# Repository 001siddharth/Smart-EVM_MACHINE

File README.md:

# Smart-EVM_MACHINE
**Approach Used** 
- We have stored the votes of each candidate in SR Latches and after the completion of 15 
sec from the first press of voters, the votes will be stored in the counter accumulating all the 
votes from different voters. At the end, you may press a push button to display the winner on 
7-Segment Display <br>
        **Features Added** <br>
  - Votes Comparator: The button named “Display Winner” when pressed compares the votes of all  
four candidates and prints ‘0’ if A wins, ‘1’ if B wins, ‘2’ if C wins, and ‘3’ if D wins. The 
comparator uses 3 four-bit comparator and 2 multiplexers
  - Display of Winner: The winner as output from comparator is shown on a 7-Segment Display for better 
readability on PCB. The Display will only function when the Display Winner button is 
pressed
  - MULTIPLE CANDIDATE VOTING: A voter may cast his vote(s) to any of the four candidates (one or more than one 
candidate) while only once for one candidate. The voter has a total time of 15 seconds in 
which he may cast his votes after which his votes will be registered
  - “Voted For” LEDs: Added four LEDs that display for which candidate the voter has voted. This feature 
removes any uncertainty in the minds of the voter that they might cast a wrong vote. A visual 
confirmation is the best way to remove any such confusion

  - REVERSE THE CASTED VOTE: As the votes are not registered into counters until 15 seconds have passed. The voter has this 15 seconds to alter his voting decisions. We have added four additional buttons to reverse a vote that voter may have casted mistakenly
    
  -  The ‘READY’ LED: As the votes are not registered into counters until 15 seconds have passed. The voter has this 15 seconds to alter his voting 
decisions. We have added four additional buttons to reverse a vote that voter may have cast mistakenly
  - 3 SECOND DELAY : 3-second delay is added after any button to cast a vote is pressed by the voter. 
This feature is to avoid any debouncing caused by the switch. However, as we are using SR 
Latch, which once set will not change its value until reset, overcomes this issue of 
debouncing without introducing any delay in the circuit.<br><br>
                                **PCB-layout**
<br><br>
Here as you can see in this PCB layout design we have generated the clock pulse of 
frequency 1Hz using N555 and with some resistors and capacitors. Each logic gate and 
IC’s VCC and GND terminal is connected with a connector with two inputs. Through pin
no.1 of the connector, we will supply VCC of 5V and Ground through pin no 2. Also, there 
is enable pin which will be activated by supplying 5V. And after enabling it will start 
comparing the votes of the candidates. And the result will be shown In the display attached.
We have done copper filling of Ground only because Filling a via with copper increases its 
thermal conductivity and higher conductivity will lead to high heat and may overheat the 
whole board and also may damage IC’s

<br> 
The Schematic of the Circuit <br>

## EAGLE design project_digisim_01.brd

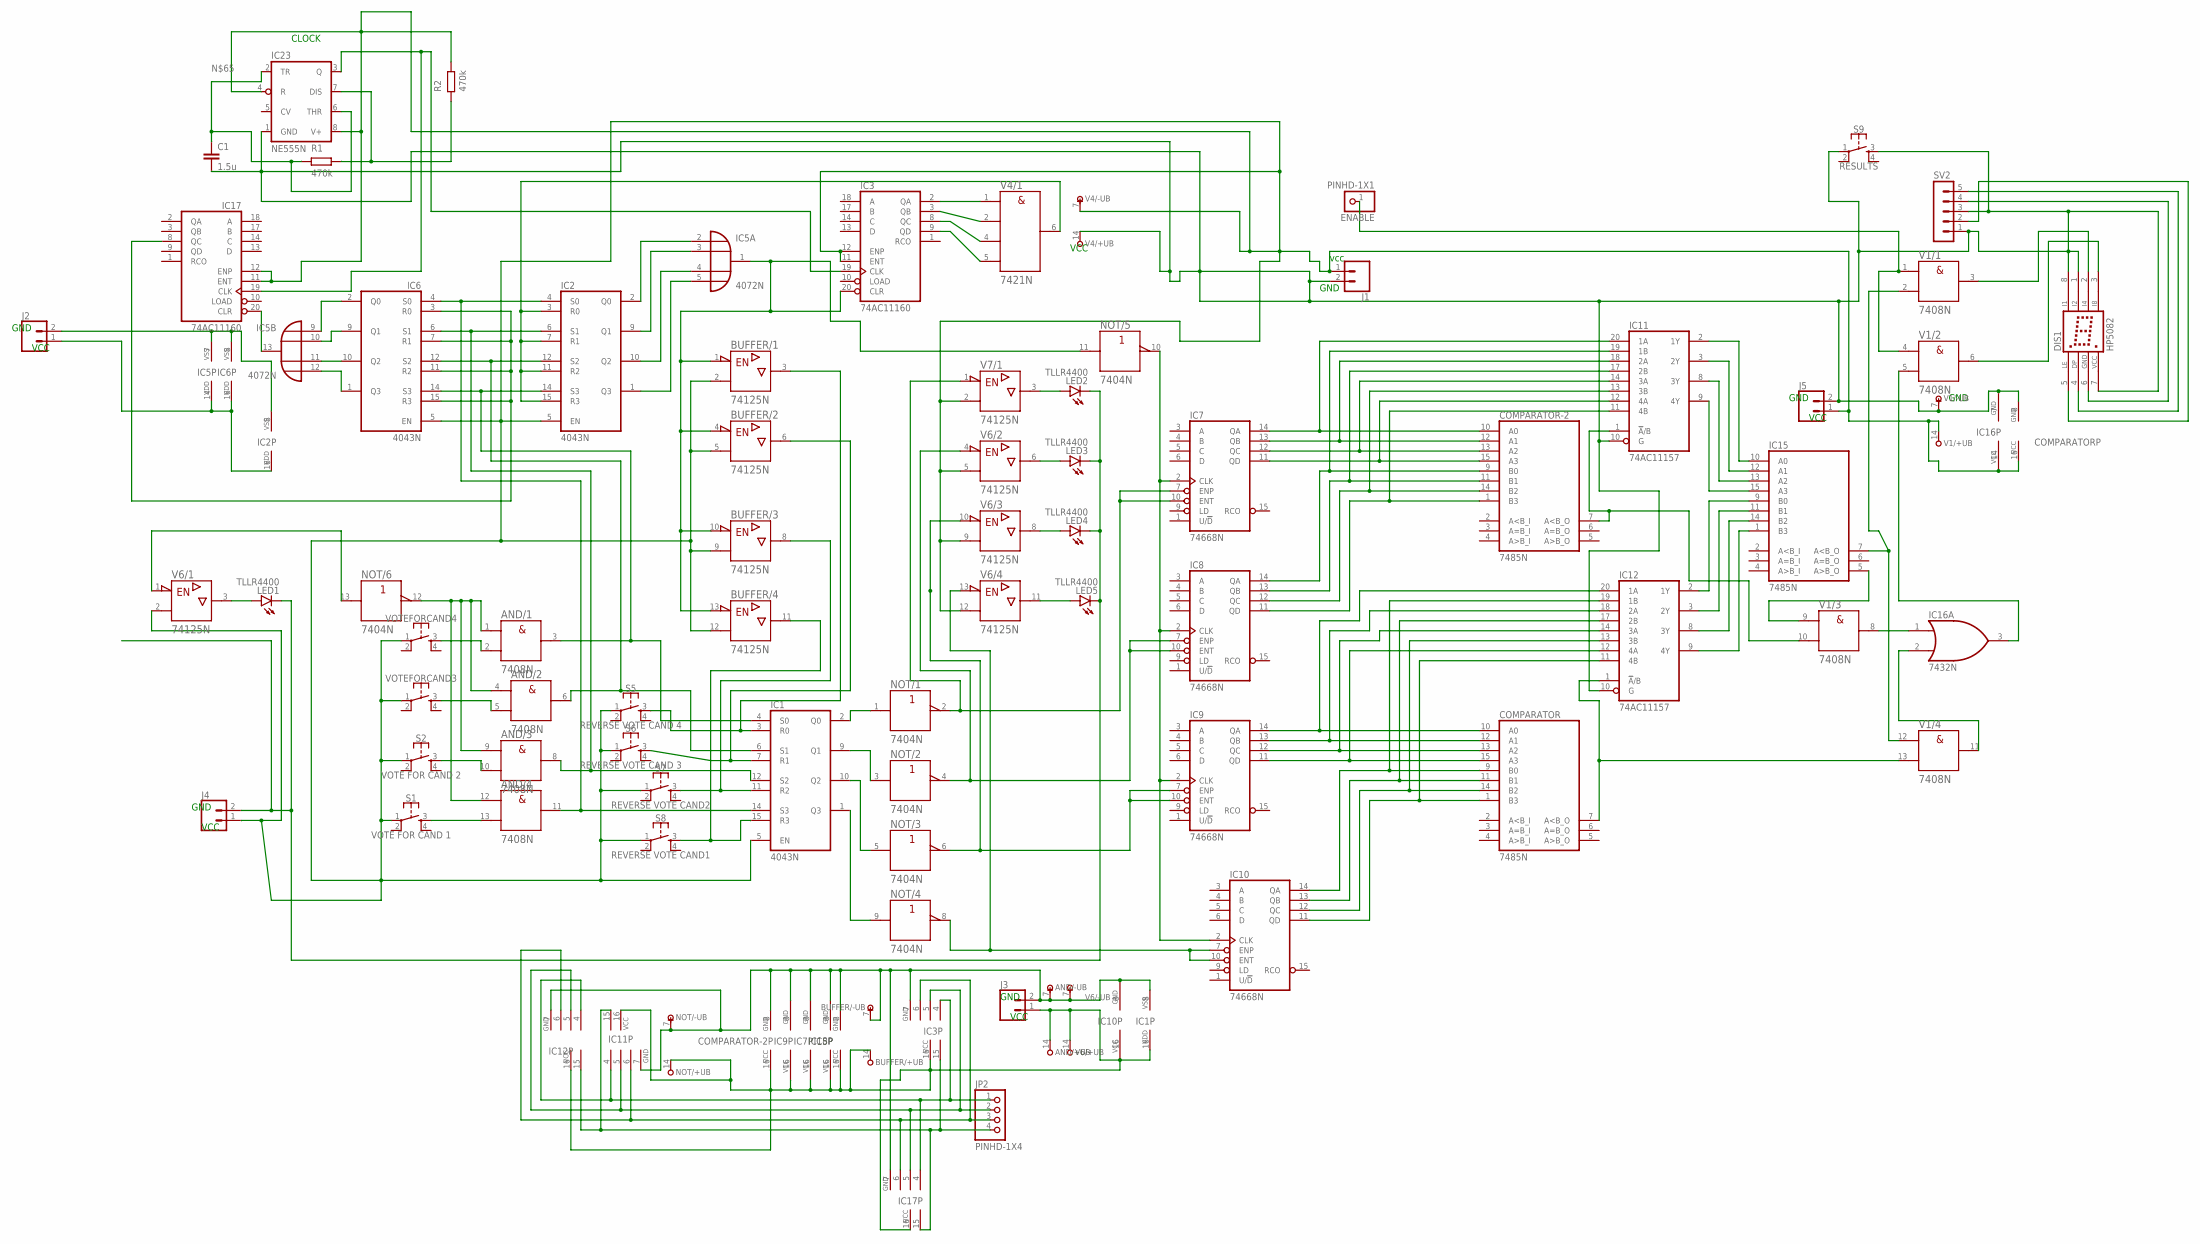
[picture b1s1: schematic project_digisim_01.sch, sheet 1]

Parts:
AND: 7408N; DIL14
BUFFER: 74125N; DIL14
C1: 1.5u; C2.5-3
COMPARATOR: 7485N; DIL16
COMPARATOR-2: 7485N; DIL16
DIS1: HP5082
ENABLE: PINHD-1X1; 1X01
IC1, IC2, IC6: 4043N; DIL16
IC3, IC17: 74AC11160; DIL20
IC5: 4072N; DIL14
IC7, IC8, IC9, IC10: 74668N; DIL16
IC11, IC12: 74AC11157; DIL20
IC15: 7485N; DIL16
IC16: 7432N; DIL14
IC23: NE555N; DIL08
J1, J2, J3, J4, J5: CONN_02LOCK; 1X02_LOCK
JP2: PINHD-1X4; 1X04
LED1, LED2, LED3, LED4, LED5: TLLR4400; LED3MM
NOT: 7404N; DIL14
S1: VOTE FOR CAND 1; TACTILE_SWITCH_SMD_4.6X2.8MM
S2: VOTE FOR CAND 2; TACTILE_SWITCH_SMD_4.6X2.8MM
S5: REVERSE VOTE CAND 4; TACTILE_SWITCH_SMD_4.6X2.8MM
S6: REVERSE VOTE CAND 3; TACTILE_SWITCH_SMD_4.6X2.8MM
S7: REVERSE VOTE CAND2; TACTILE_SWITCH_SMD_4.6X2.8MM
S8: REVERSE VOTE CAND1; TACTILE_SWITCH_SMD_4.6X2.8MM
S9: RESULTS; TACTILE_SWITCH_SMD_4.6X2.8MM
SV2: MA05-1
V1: 7408N; DIL14
V4: 7421N; DIL14
V6, V7: 74125N; DIL14
VOTEFORCAND3, VOTEFORCAND4: MOMENTARY-SWITCH-SPST-2-SMD-4.6X2.8MM; TACTILE_SWITCH_SMD_4.6X2.8MM

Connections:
+UB: V7.14 (+UB)
-UB: V7.7 (-UB)
unnamed: AND.3 (Y), IC1.4 (S0), IC2.14 (S3), IC6.14 (S3)
unnamed: IC10.7 (ENP), IC10.10 (ENT), NOT.8 (Y), V6.13 (!G)
unnamed: IC2.2 (Q0), IC5.2 (I0)
unnamed: AND.8 (Y), IC1.12 (S2), IC2.6 (S1), IC6.6 (S1)
unnamed: DIS1.3 (I8), V1.6 (Y)
unnamed: BUFFER.3 (Y), IC1.3 (R0), S5.3
unnamed: BUFFER.6 (Y), IC1.7 (R1), S6.3
unnamed: BUFFER.11 (Y), IC1.15 (R3), S8.3
unnamed: IC1.2 (Q0), NOT.1 (A)
unnamed: IC1.9 (Q1), NOT.3 (A)
unnamed: NOT.13 (A), V6.1 (!G)
unnamed: IC1.10 (Q2), NOT.5 (A)
unnamed: LED2.A, V7.3 (Y)
unnamed: IC1.1 (Q3), NOT.9 (A)
unnamed: LED3.A, V6.6 (Y)
unnamed: IC7.7 (ENP), IC7.10 (ENT), NOT.2 (Y), V7.1 (!G)
unnamed: IC16.1 (I0), V1.8 (Y)
unnamed: IC2.8 (VSS), IC5.7 (VSS), IC6.8 (VSS), J2.2
unnamed: COMPARATOR-2.10 (A0), IC7.14 (QA), IC11.20 (1A)
unnamed: COMPARATOR-2.12 (A1), IC7.13 (QB), IC11.18 (2A)
unnamed: LED4.A, V6.8 (Y)
unnamed: COMPARATOR-2.13 (A2), IC7.12 (QC), IC11.14 (3A)
unnamed: COMPARATOR-2.15 (A3), IC7.11 (QD), IC11.12 (4A)
unnamed: COMPARATOR-2.9 (B0), IC8.14 (QA), IC11.19 (1B)
unnamed: COMPARATOR-2.11 (B1), IC8.13 (QB), IC11.17 (2B)
unnamed: COMPARATOR-2.14 (B2), IC8.12 (QC), IC11.13 (3B)
unnamed: COMPARATOR-2.1 (B3), IC8.11 (QD), IC11.11 (4B)
unnamed: COMPARATOR.10 (A0), IC9.14 (QA), IC12.20 (1A)
unnamed: COMPARATOR.12 (A1), IC9.13 (QB), IC12.18 (2A)
unnamed: COMPARATOR.13 (A2), IC9.12 (QC), IC12.14 (3A)
unnamed: COMPARATOR.15 (A3), IC9.11 (QD), IC12.12 (4A)
unnamed: COMPARATOR.9 (B0), IC10.14 (QA), IC12.19 (1B)
unnamed: COMPARATOR.11 (B1), IC10.13 (QB), IC12.17 (2B)
unnamed: COMPARATOR.14 (B2), IC10.12 (QC), IC12.13 (3B)
unnamed: COMPARATOR.1 (B3), IC10.11 (QD), IC12.11 (4B)
unnamed: IC11.2 (1Y), IC15.10 (A0)
unnamed: IC11.3 (2Y), IC15.12 (A1)
unnamed: IC11.8 (3Y), IC15.13 (A2)
unnamed: IC11.9 (4Y), IC15.15 (A3)
unnamed: IC12.2 (1Y), IC15.9 (B0)
unnamed: IC12.3 (2Y), IC15.11 (B1)
unnamed: IC12.8 (3Y), IC15.14 (B2)
unnamed: IC12.9 (4Y), IC15.1 (B3)
unnamed: COMPARATOR-2.7 (A<B_O), IC11.1 (!A!/B), V1.10 (B)
unnamed: COMPARATOR.7 (A<B_O), IC12.1 (!A!/B), V1.13 (B)
unnamed: AND.11 (Y), IC1.14 (S3), IC2.4 (S0), IC6.4 (S0)
unnamed: IC15.5 (A>B_O), V1.9 (A)
unnamed: ENABLE.1, V1.1 (A), V1.4 (A)
unnamed: IC2.16 (VDD), IC5.14 (VDD), IC6.16 (VDD), J2.1
unnamed: IC16.2 (I1), V1.11 (Y)
unnamed: IC3.19 (CLK), IC17.19 (CLK), IC23.3 (Q)
unnamed: IC2.9 (Q1), IC5.3 (I1)
unnamed: IC2.10 (Q2), IC5.4 (I2)
unnamed: IC2.1 (Q3), IC5.5 (I3)
unnamed: BUFFER.8 (Y), IC1.11 (R2), S7.3
unnamed: LED5.A, V6.11 (Y)
unnamed: IC16.3 (O), V1.5 (B)
unnamed: IC8.7 (ENP), IC8.10 (ENT), NOT.4 (Y), V6.4 (!G)
unnamed: DIS1.2 (I4), V1.3 (Y)
unnamed: IC7.2 (CLK), IC8.2 (CLK), IC9.2 (CLK), IC10.2 (CLK), NOT.10 (Y)
unnamed: J4.2, LED1.K (C), LED2.K (C), LED3.K (C), LED4.K (C), LED5.K (C)
unnamed: IC15.7 (A<B_O), V1.2 (B), V1.12 (A)
unnamed: AND.6 (Y), IC1.6 (S1), IC2.12 (S2), IC6.12 (S2)
unnamed: LED1.A, V6.3 (Y)
unnamed: C1.1, IC23.2 (TR), IC23.6 (THR)
unnamed: AND.2 (B), VOTEFORCAND4.3
unnamed: AND.5 (B), VOTEFORCAND3.3
unnamed: AND.10 (B), S2.3
unnamed: AND.13 (B), S1.3
unnamed: AND.1 (A), AND.4 (A), AND.9 (A), AND.12 (A), NOT.12 (Y)
unnamed: IC3.2 (QA), V4.1 (A)
unnamed: IC3.3 (QB), V4.2 (B)
unnamed: IC3.8 (QC), V4.4 (C)
unnamed: IC3.9 (QD), V4.5 (D)
unnamed: IC2.3 (R0), IC2.7 (R1), IC2.11 (R2), IC2.15 (R3), V4.6 (Y)
unnamed: IC5.13 (O), IC17.20 (CLR)
unnamed: IC5.9 (I0), IC6.2 (Q0)
unnamed: IC5.10 (I1), IC6.9 (Q1)
unnamed: IC5.11 (I2), IC6.10 (Q2)
unnamed: IC5.12 (I3), IC6.1 (Q3)
unnamed: IC6.3 (R0), IC6.7 (R1), IC6.11 (R2), IC6.15 (R3), IC17.8 (QC)
unnamed: BUFFER.2 (A), BUFFER.5 (A), BUFFER.9 (A), BUFFER.12 (A), COMPARATOR.16 (VCC), IC1.5 (EN), IC2.5 (EN), IC3.11 (ENT), IC3.12 (ENP), IC6.5 (EN), IC16.14 (VCC), IC17.11 (ENT), IC17.12 (ENP), IC23.4 (R), IC23.8 (V+), J1.1, J4.1, J5.1, S1.1, S2.1, S5.1, S6.1, S7.1, S8.1, V1.14 (+UB), V4.7 (-UB), V6.2 (A), V6.5 (A), V6.9 (A), V6.12 (A), V7.2 (A), VOTEFORCAND3.1, VOTEFORCAND4.1
unnamed: IC9.7 (ENP), IC9.10 (ENT), NOT.6 (Y), V6.10 (!G)
unnamed: C1.2, COMPARATOR.8 (GND), DIS1.1 (I2), DIS1.7 (VCC), DIS1.8 (I1), IC11.10 (G), IC12.10 (G), IC16.7 (GND), IC23.1 (GND), J1.2, J5.2, S9.1, S9.3, SV2.1, SV2.3, V1.7 (-UB), V4.14 (+UB)
unnamed: DIS1.6 (GND), SV2.4
unnamed: DIS1.4 (DP), SV2.5
unnamed: BUFFER.1 (!G), BUFFER.4 (!G), BUFFER.10 (!G), BUFFER.13 (!G), IC3.20 (CLR), IC5.1 (O), NOT.11 (A)
unnamed: DIS1.5 (LE), SV2.2
unnamed: AND.7 (-UB), BUFFER.7 (-UB), COMPARATOR-2.8 (GND), IC1.8 (VSS), IC3.7 (GND), IC7.8 (GND), IC8.8 (GND), IC9.8 (GND), IC10.8 (GND), IC11.7 (GND), IC12.7 (GND), IC15.8 (GND), IC17.7 (GND), J3.2, NOT.7 (-UB), V6.7 (-UB)
unnamed: AND.14 (+UB), BUFFER.14 (+UB), COMPARATOR-2.16 (VCC), IC1.16 (VDD), IC3.16 (VCC), IC7.16 (VCC), IC8.16 (VCC), IC9.16 (VCC), IC10.16 (VCC), IC11.16 (VCC), IC12.16 (VCC), IC15.16 (VCC), IC17.16 (VCC), J3.1, NOT.14 (+UB), V6.14 (+UB)
unnamed: IC3.4 (GND), IC11.4 (GND), IC12.4 (GND), IC17.4 (GND), JP2.1
unnamed: IC3.5 (GND), IC11.5 (GND), IC12.5 (GND), IC17.5 (GND), JP2.2
unnamed: IC3.15 (VCC), IC11.15 (VCC), IC12.15 (VCC), IC17.15 (VCC), JP2.4
unnamed: IC3.6 (GND), IC11.6 (GND), IC12.6 (GND), IC17.6 (GND), JP2.3

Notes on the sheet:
CLOCK
vcc
GND
VCC

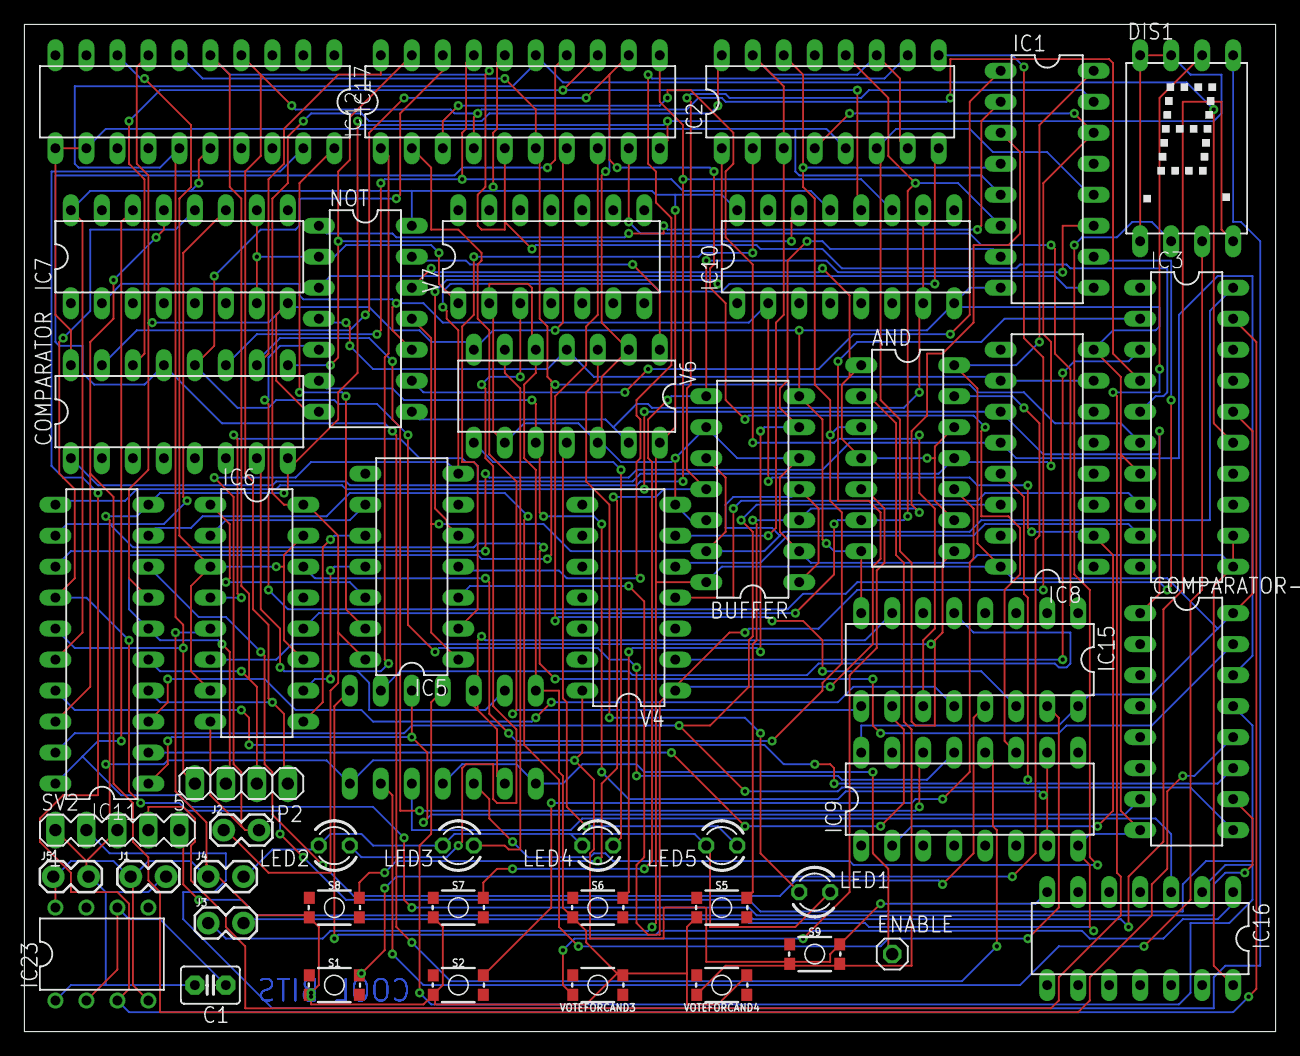
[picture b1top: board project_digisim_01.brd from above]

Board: 2 copper layers, 102.5 x 82.5 mm, 48 parts (1 on the bottom side), 94 nets.

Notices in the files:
parts and their libraries:
SparkFun-Connectors: Licensing: Creative Commons ShareAlike 4.0 International - https://creativecommons.org/licenses/by-sa/4.0
